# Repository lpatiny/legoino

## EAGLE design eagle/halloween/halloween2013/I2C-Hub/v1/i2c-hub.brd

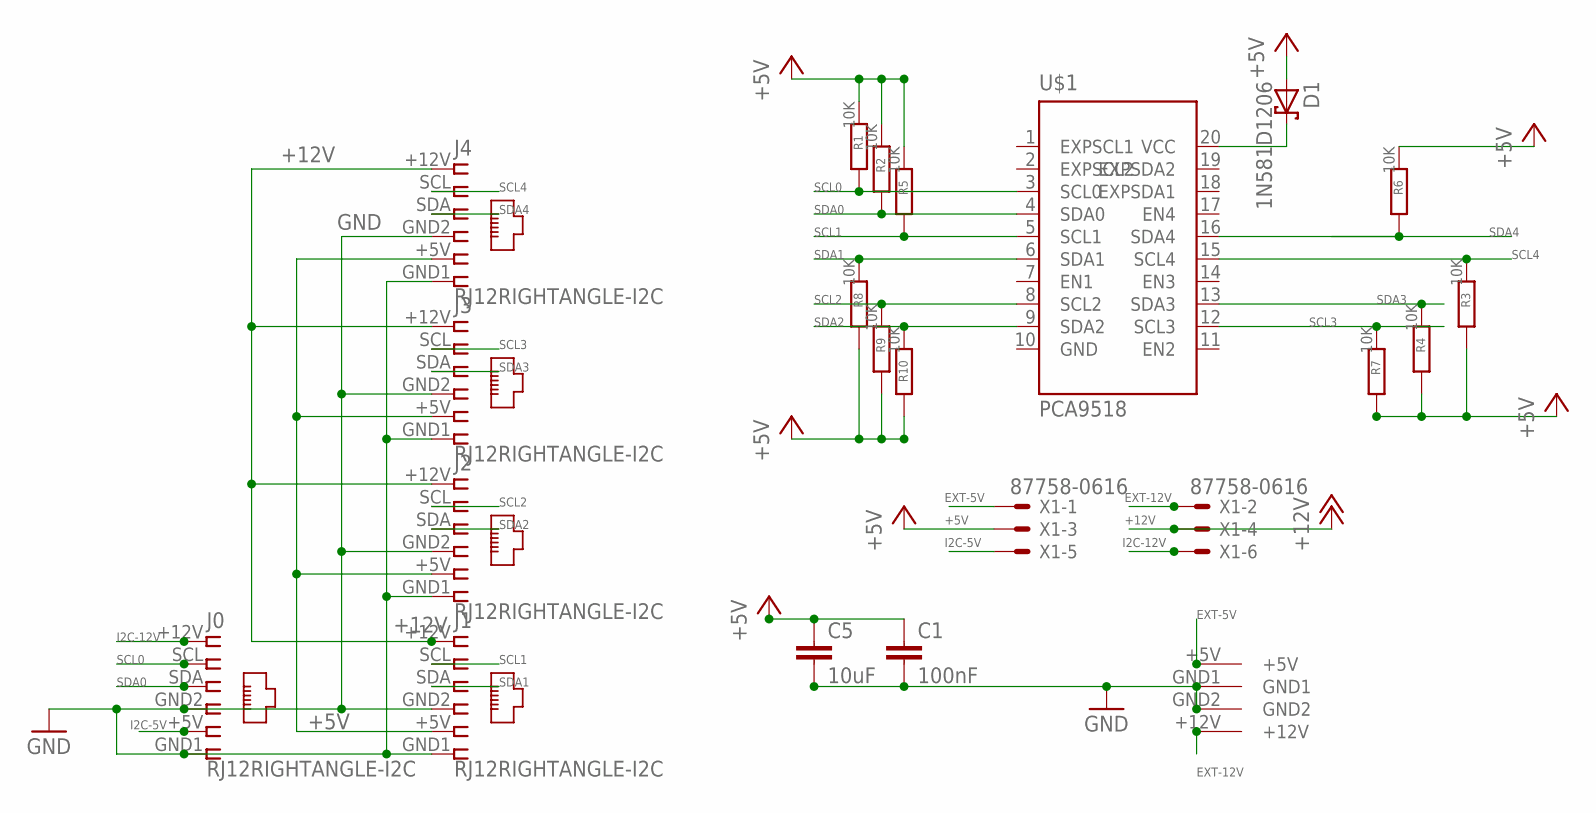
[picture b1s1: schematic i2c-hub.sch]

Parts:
C1: 100nF; C1206
C5: 10uF; C1206
D1: 1N581D1206; LED-1206
J0, J1, J2, J3, J4: RJ12RIGHTANGLE-I2C; RJ12-RIGHTANGLE-I2C
R1, R2, R3, R4, R5, R6, R7, R8, R9, R10: 10K; M1206
U$1: PCA9518; SO20W
U$2: KPJX-4S-S
X1: 87758-0616

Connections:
+5V: C1.1, C5.1, D1.A, J1.+5V (5), J2.+5V (5), J3.+5V (5), J4.+5V (5), R1.1, R2.1, R3.2, R4.2, R5.1, R6.1, R7.2, R8.2, R9.2, R10.2, X1.3
+5V1: D1.C, U$1.20 (VCC)
+12V: J1.+12V (1), J2.+12V (1), J3.+12V (1), J4.+12V (1), X1.4
EXT-5V: U$2.+5V, X1.1
EXT-12V: U$2.+12V, X1.2
GND: C1.2, C5.2, J0.GND1 (6), J0.GND2 (4), J1.GND1 (6), J1.GND2 (4), J2.GND1 (6), J2.GND2 (4), J3.GND1 (6), J3.GND2 (4), J4.GND1 (6), J4.GND2 (4), U$1.10 (GND), U$2.GND1, U$2.GND2
I2C-5V: J0.+5V (5), X1.5
I2C-12V: J0.+12V (1), X1.6
SCL0: J0.SCL (2), R1.2, U$1.3 (SCL0)
SCL1: J1.SCL (2), R5.2, U$1.5 (SCL1)
SCL2: J2.SCL (2), R9.1, U$1.8 (SCL2)
SCL3: J3.SCL (2), R7.1, U$1.12 (SCL3)
SCL4: J4.SCL (2), R3.1, U$1.15 (SCL4)
SDA0: J0.SDA (3), R2.2, U$1.4 (SDA0)
SDA1: J1.SDA (3), R8.1, U$1.6 (SDA1)
SDA2: J2.SDA (3), R10.1, U$1.9 (SDA2)
SDA3: J3.SDA (3), R4.1, U$1.13 (SDA3)
SDA4: J4.SDA (3), R6.2, U$1.16 (SDA4)

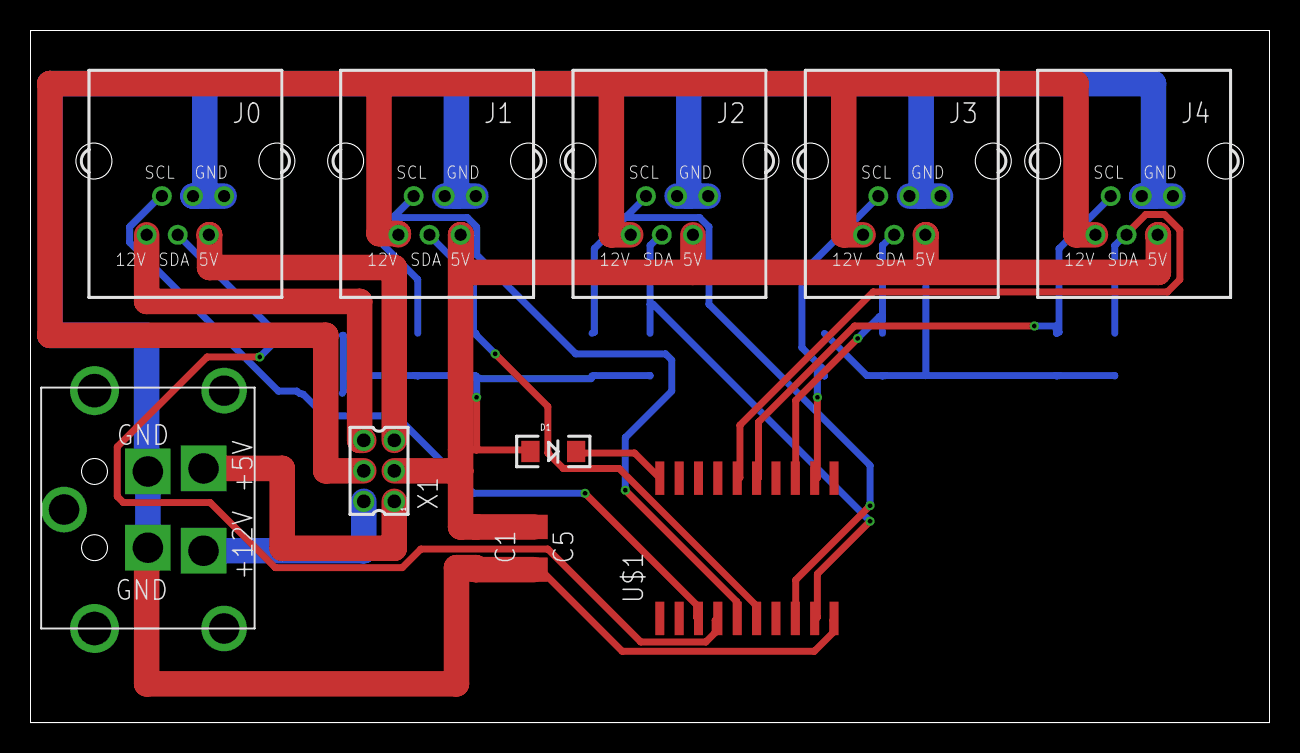
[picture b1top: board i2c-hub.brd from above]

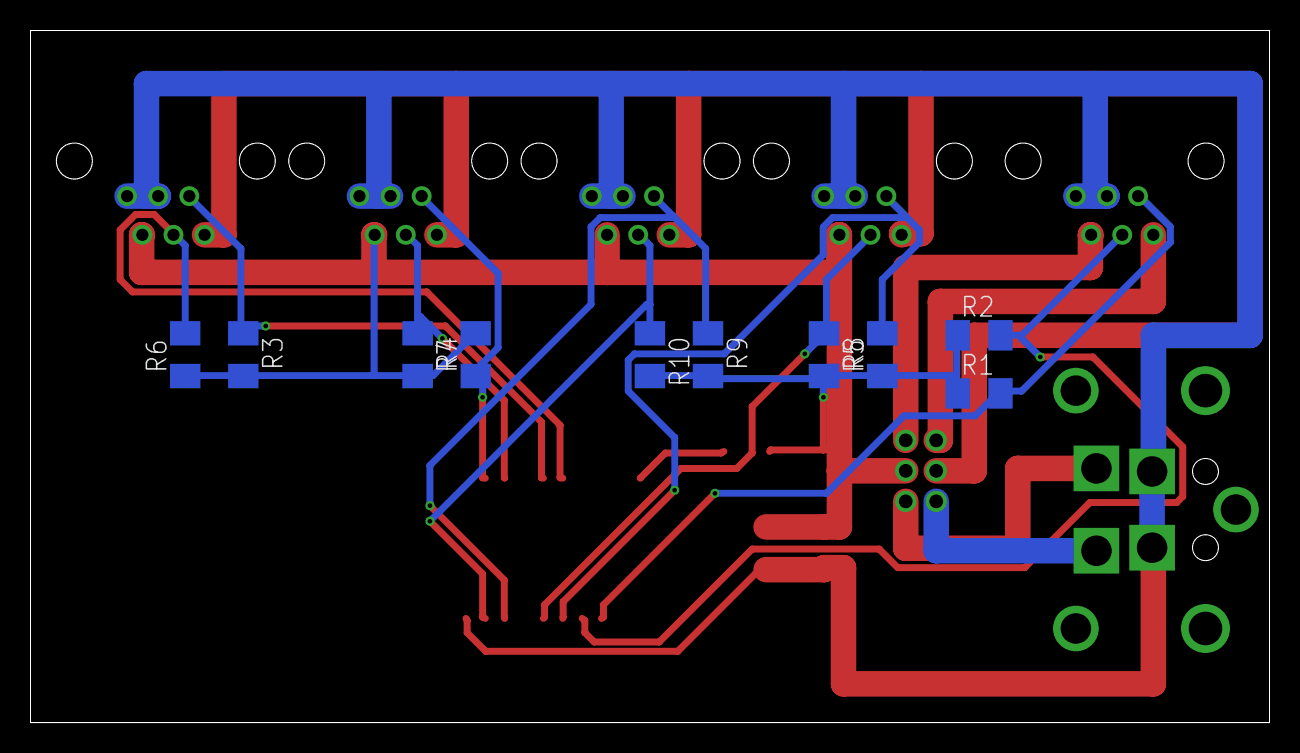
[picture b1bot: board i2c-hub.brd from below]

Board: 2 copper layers, 81.3 x 45.4 mm, 21 parts (10 on the bottom side), 18 nets.

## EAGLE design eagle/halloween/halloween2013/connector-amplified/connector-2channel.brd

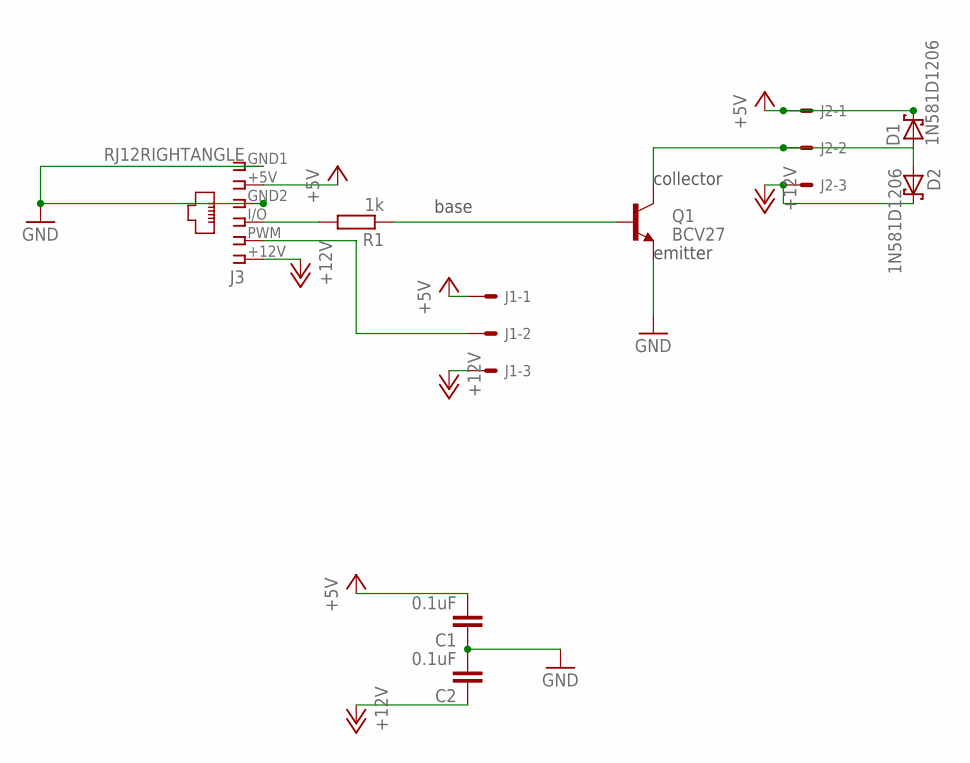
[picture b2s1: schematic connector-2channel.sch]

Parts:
C1, C2: 0.1uF; C1206
D1, D2: 1N581D1206; LED-1206
J1, J2: 22-27-2031-03; 6410-03
J3: RJ12RIGHTANGLE; RJ12-RIGHTANGLE
Q1: BCV27; SOT23
R1: 1k; M1206

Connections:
+5V: C1.2, D1.C, J1.1, J2.1, J3.+5V (5)
+12V: C2.1, D2.C, J1.3, J2.3, J3.+12V (1)
GND: C1.1, C2.2, J3.GND1 (6), J3.GND2 (4), Q1.2 (E)
unnamed: Q1.1 (B), R1.1
unnamed: J3.I/O (3), R1.2
unnamed: J1.2, J3.PWM (2)
unnamed: D1.A, D2.A, J2.2, Q1.3 (C)

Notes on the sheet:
base
collector
emitter

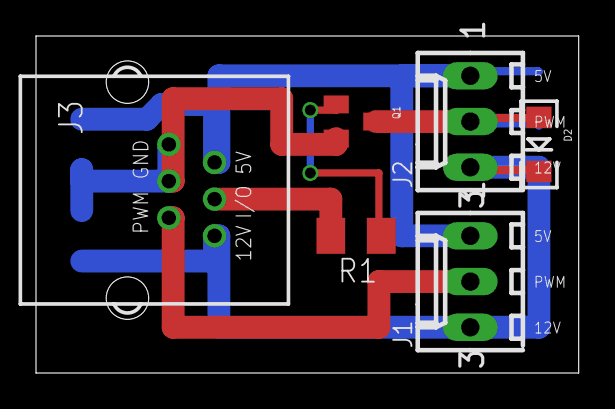
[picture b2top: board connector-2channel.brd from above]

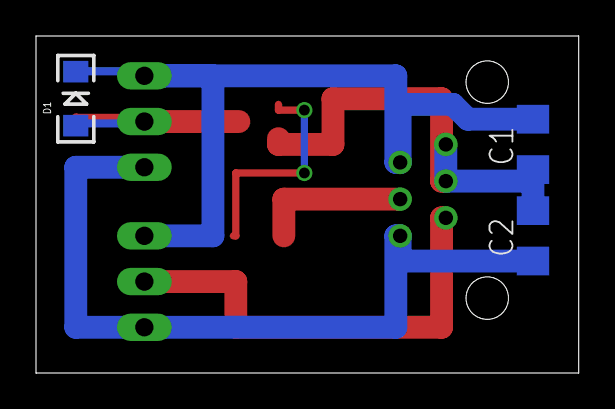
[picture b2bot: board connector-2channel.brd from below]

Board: 2 copper layers, 30.1 x 18.7 mm, 9 parts (3 on the bottom side), 7 nets.

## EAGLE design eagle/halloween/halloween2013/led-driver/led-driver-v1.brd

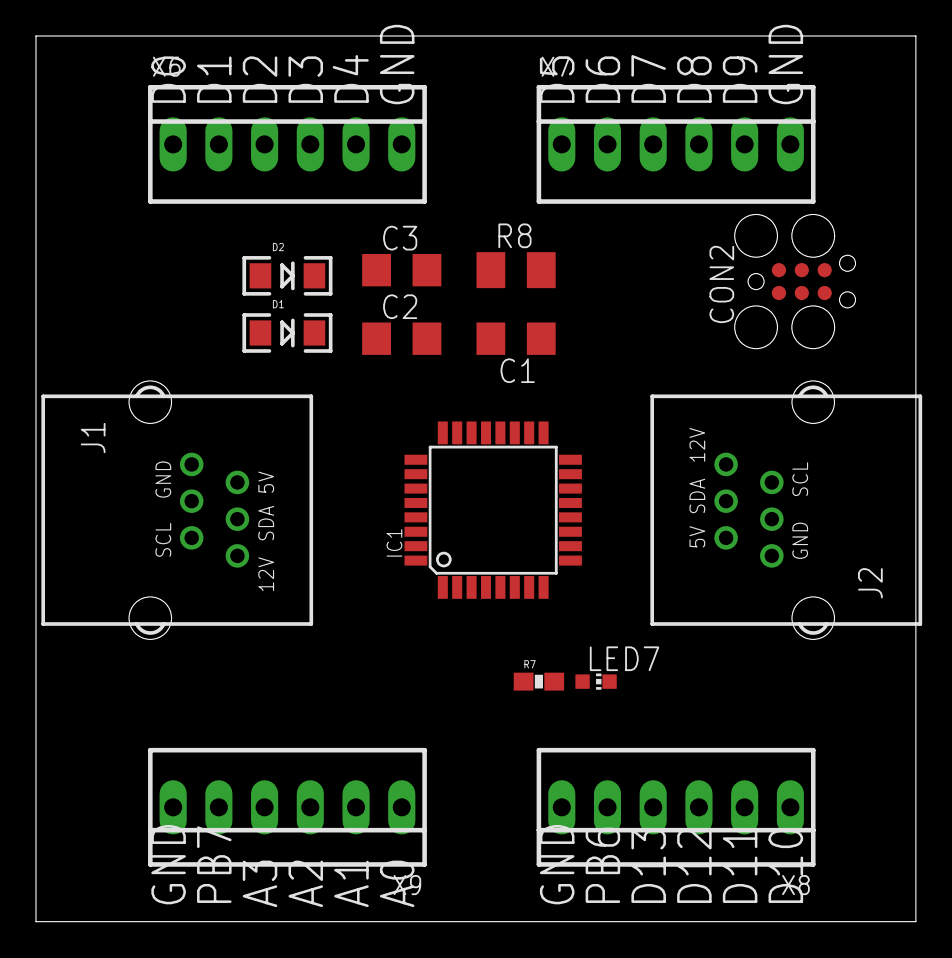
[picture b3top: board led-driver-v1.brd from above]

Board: 2 copper layers, 48.9 x 49.2 mm, 16 parts (0 on the bottom side), 30 nets, no tracks yet.

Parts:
C1, C2: 0.1uF; C1206
C3: 10uF; C1206
CON2: TC2030-MCP
D1, D2: 1N581D1206; LED-1206
IC1: MEGA8-AI; TQFP32-08
J1, J2: RJ12RIGHTANGLE-I2C; RJ12-RIGHTANGLE-I2C
LED7: CHIP-LED0603
R7: 10k; 0603-RES
R8: 10k; M1206
X6, X7, X8, X9: 22-23-2061

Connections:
5V_A: CON2.5V, D1.A
5V_B: D2.A, J1.+5V, J2.+5V
+5V: C1.1, C2.1, C3.1, D1.C, D2.C, IC1.4, IC1.6, IC1.18, R7.1, R8.2
A0: IC1.23, X9.1
A1: IC1.24, X9.2
A2: IC1.25, X9.3
A3: IC1.26, X9.4
D0: IC1.30, X6.1
D1: IC1.31, X6.2
D2: IC1.32, X6.3
D3: IC1.1, X6.4
D4: IC1.2, X6.5
D5: IC1.9, X7.1
D6: IC1.10, X7.2
D7: IC1.11, X7.3
D8: IC1.12, X7.4
D9: IC1.13, X7.5
D10: IC1.14, X8.1
GND: C2.2, C3.2, CON2.GND, IC1.3, IC1.5, IC1.21, J1.GND1, J1.GND2, J2.GND1, J2.GND2, LED7.C, X6.6, X7.6, X8.6, X9.6
MISO: CON2.MISO, IC1.16, X8.3
MOSI: CON2.MOSI, IC1.15, X8.2
unnamed: C1.2, IC1.20
unnamed: J1.+12V, J2.+12V
unnamed: LED7.A, R7.2
PB6: IC1.7, X8.5
PB7: IC1.8, X9.5
RESET: CON2.RESET, IC1.29, R8.1
SCK: CON2.SCK, IC1.17, X8.4
SCL: IC1.28, J1.SCL, J2.SCL
SDA: IC1.27, J1.SDA, J2.SDA

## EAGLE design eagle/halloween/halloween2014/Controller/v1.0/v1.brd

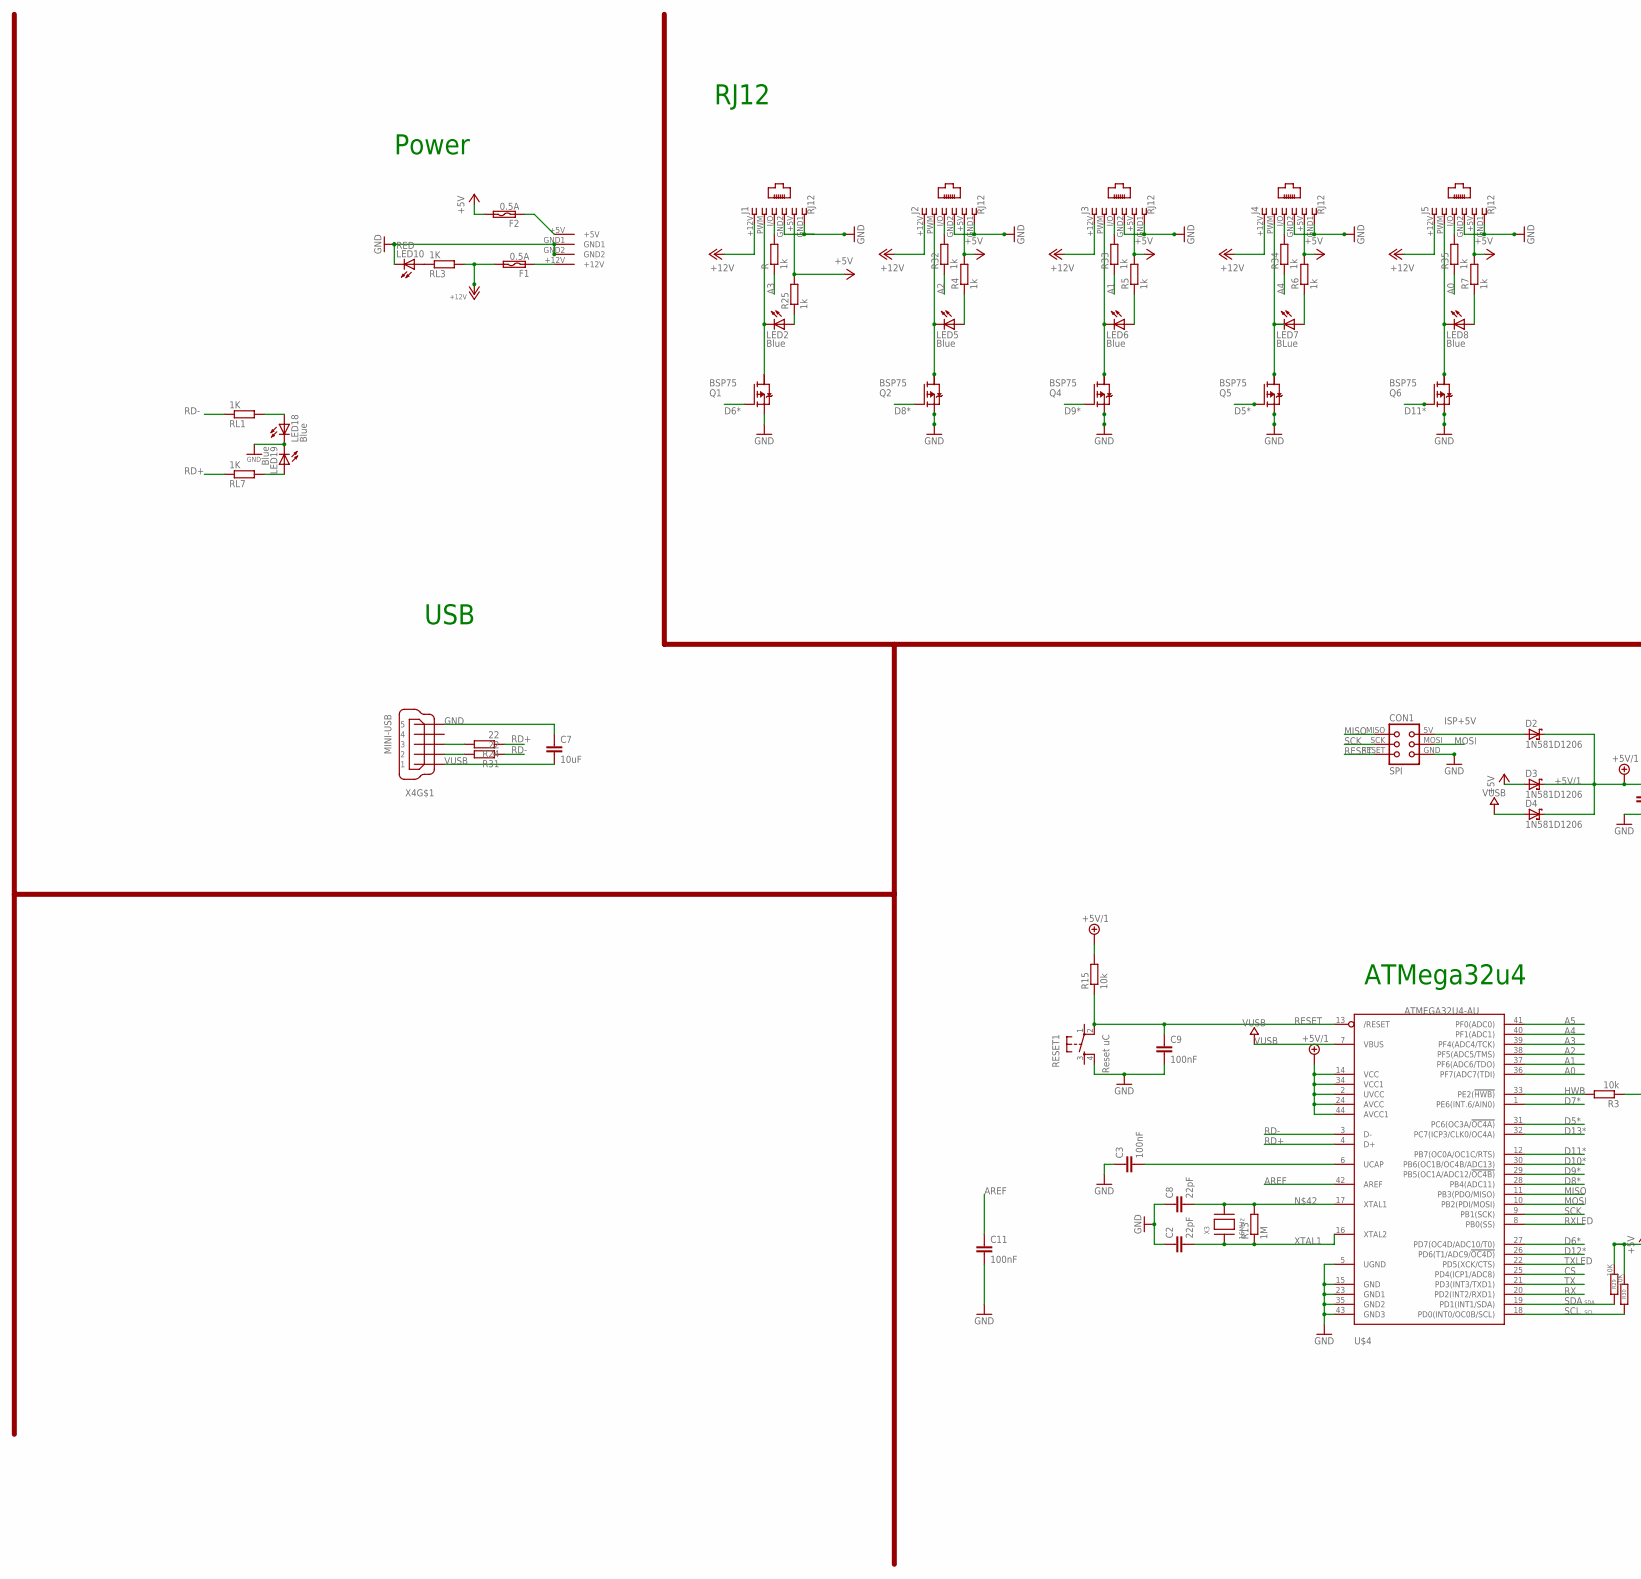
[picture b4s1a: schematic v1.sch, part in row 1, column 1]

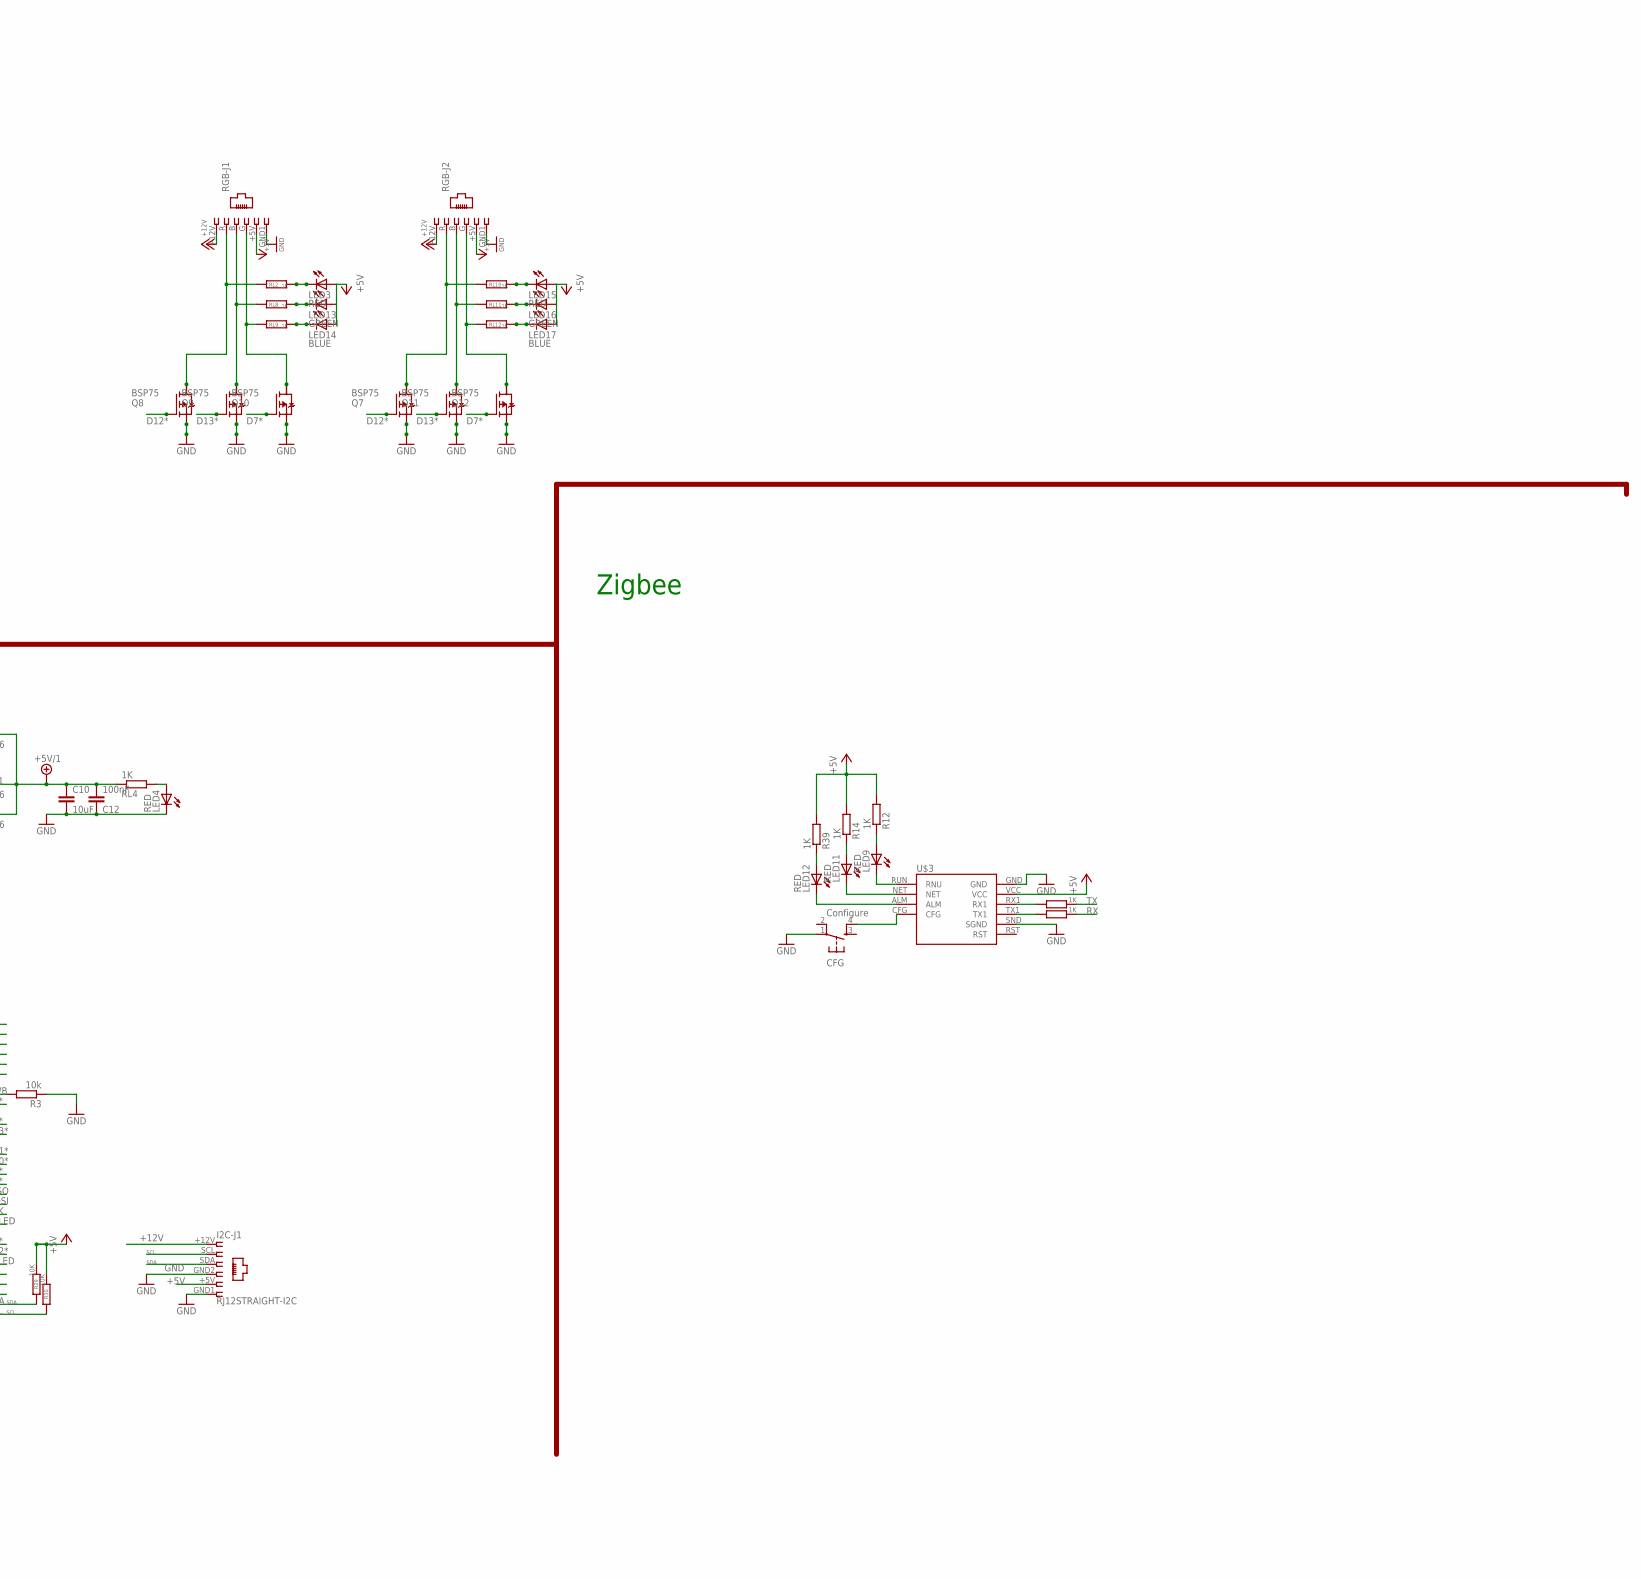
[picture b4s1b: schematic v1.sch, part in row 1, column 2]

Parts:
C2, C8: 22pF; C1206
C3, C9, C11, C12: 100nF; C1206
C7, C10: 10uF; C1206
CFG: Configure; TACTILE_SWITCH_SMD
CON1: SPI; TC2030-MCP-NL
D2, D3, D4: 1N581D1206; LED-1206
F1, F2: 0.5A; C1812
I2C-J1: RJ12STRAIGHT-I2C; RJ12-STRAIGHT-I2C
J1, J2, J3, J4, J5: RJ12; RJ12-STRAIGHT
LED2, LED5, LED6, LED8, LED18, LED19: Blue; CHIPLED_1206
LED3, LED4, LED10, LED15: RED; CHIPLED_1206
LED7: BLue; CHIPLED_1206
LED9, LED11, LED12: RED; CHIP-LED0805
LED13, LED16: GREEN; CHIPLED_1206
LED14, LED17: BLUE; CHIPLED_1206
Q1, Q2, Q4, Q5, Q6, Q7, Q8, Q9, Q10, Q11, Q12: BSP75; PG-SOT-223
R, R4, R5, R6, R7, R25, R32, R33, R34, R35: 1k; R0805
R3, R15: 10k; M0805
R8, R11, R12, R14, R39: 1K; R0805
R13: 1M; R1206
R24, R31: 22; M1206
R29, R30: 10K; M0805
RESET1: Reset uC; TACTILE_SWITCH_SMD
RGB-J1, RGB-J2: RJ12; RJ12-STRAIGHT-RGB
RL1, RL3, RL4, RL7: 1K; R0805
RL2, RL8, RL9, RL10, RL11, RL12: 1K; M0805
U$3: SZ05-ZIGBEESMD; SZ05-ZIGBEE3
U$4: ATMEGA32U4-AU; TQFP44
U$6: KPJX-4S-S
X3: 16MHz; NX6035
X4: MINI-USB; 32005-201

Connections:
+5V: D3.A, F2.2, I2C-J1.+5V (5), J1.+5V (5), J2.+5V (5), J3.+5V (5), J4.+5V (5), J5.+5V (5), LED3.A, LED13.A, LED14.A, LED15.A, LED16.A, LED17.A, R4.2, R5.2, R6.2, R7.2, R12.2, R14.2, R25.2, R29.1, R30.1, R39.2, RGB-J1.+5V (5), RGB-J2.+5V (5), U$3.VCC
+5V/1: C10.1, C12.2, D2.C, D3.C, D4.C, R15.2, RL4.1, U$4.2 (UVCC), U$4.14 (VCC), U$4.24 (AVCC), U$4.34 (VCC1), U$4.44 (AVCC1)
+12V: F1.2, I2C-J1.+12V (1), J1.+12V (1), J2.+12V (1), J3.+12V (1), J4.+12V (1), J5.+12V (1), RGB-J1.+12V (1), RGB-J2.+12V (1), RL3.2
A0: R35.1, U$4.36 (PF7(ADC7(TDI))
A1: R33.1, U$4.37 (PF6(ADC6/TDO))
A2: R32.1, U$4.38 (PF5(ADC5/TMS))
A3: R.1, U$4.39 (PF4(ADC4/TCK))
A4: R34.1, U$4.40 (PF1(ADC1))
A5: U$4.41 (PF0(ADC0))
AREF: C11.1, U$4.42 (AREF)
CS: U$4.25 (PD4(ICP1/ADC8))
D5*: Q5.1 (G), U$4.31 (PC6(OC3A/!OC4A))
D6*: Q1.1 (G), U$4.27 (PD7(OC4D/ADC10/T0))
D7*: Q10.1 (G), Q12.1 (G), U$4.1 (PE6(INT.6/AIN0))
D8*: Q2.1 (G), U$4.28 (PB4(ADC11))
D9*: Q4.1 (G), U$4.29 (PB5(OC1A/ADC12/!OC4B))
D10*: U$4.30 (PB6(OC1B/OC4B/ADC13))
D11*: Q6.1 (G), U$4.12 (PB7(OC0A/OC1C/RTS))
D12*: Q7.1 (G), Q8.1 (G), U$4.26 (PD6(T1/ADC9/!OC4D))
D13*: Q9.1 (G), Q11.1 (G), U$4.32 (PC7(ICP3/CLK0/OC4A))
D+USB: R24.2, X4.3
D-USB: R31.2, X4.2
GND: C2.1, C3.1, C7.1, C8.1, C9.2, C10.2, C11.2, C12.1, CFG.1, CON1.GND, I2C-J1.GND1 (6), I2C-J1.GND2 (4), J1.GND1 (6), J1.GND2 (4), J2.GND1 (6), J2.GND2 (4), J3.GND1 (6), J3.GND2 (4), J4.GND1 (6), J4.GND2 (4), J5.GND1 (6), J5.GND2 (4), LED4.C, LED10.C, LED18.C, LED19.C, Q1.3 (S), Q2.3 (S), Q4.3 (S), Q5.3 (S), Q6.3 (S), Q7.3 (S), Q8.3 (S), Q9.3 (S), Q10.3 (S), Q11.3 (S), Q12.3 (S), R3.1, RESET1.4, RGB-J1.GND1 (6), RGB-J2.GND1 (6), U$3.GND, U$3.SND (SGND), U$4.5 (UGND), U$4.15 (GND), U$4.23 (GND1), U$4.35 (GND2), U$4.43 (GND3), U$6.GND1, U$6.GND2, X4.5
GND1: LED9.C, U$3.RUN (RNU)
GND2: LED11.C, U$3.NET
GND3: LED12.C, U$3.ALM
HWB: R3.2, U$4.33 (PE2(!HWB))
ISP+5V: CON1.5V (VCC), D2.A
MISO: CON1.MISO, U$4.11 (PB3(PDO/MISO))
MOSI: CON1.MOSI, U$4.10 (PB2(PDI/MOSI))
unnamed: J3.PWM (2), LED6.C, Q4.2 (D)
unnamed: J2.I/O (3), R32.2
unnamed: LED5.A, R4.1
unnamed: J4.PWM (2), LED7.C, Q5.2 (D)
unnamed: Q10.2 (D), RGB-J1.G (4), RL9.1
unnamed: J3.I/O (3), R33.2
unnamed: LED18.A, RL1.2
unnamed: Q11.2 (D), RGB-J2.B (3), RL11.1
unnamed: R11.2, U$3.RX1
unnamed: LED4.A, RL4.2
unnamed: LED19.A, RL7.2
unnamed: C3.2, U$4.6 (UCAP)
unnamed: LED2.A, R25.1
unnamed: J1.I/O (3), R.2
unnamed: J5.PWM (2), LED8.C, Q6.2 (D)
unnamed: Q7.2 (D), RGB-J2.R (2), RL10.1
unnamed: LED6.A, R5.1
unnamed: Q12.2 (D), RGB-J2.G (4), RL12.1
unnamed: R8.2, U$3.TX1
unnamed: LED9.A, R12.1
unnamed: LED11.A, R14.1
unnamed: LED12.A, R39.1
unnamed: J2.PWM (2), LED5.C, Q2.2 (D)
unnamed: J4.I/O (3), R34.2
unnamed: LED7.A, R6.1
unnamed: LED15.C, RL10.2
unnamed: J5.I/O (3), R35.2
unnamed: LED8.A, R7.1
unnamed: J1.PWM (2), LED2.C, Q1.2 (D)
unnamed: CFG.4, U$3.CFG
unnamed: LED3.C, RL2.2
unnamed: LED13.C, RL8.2
unnamed: F2.1, U$6.+5V
unnamed: F1.1, U$6.+12V
unnamed: LED14.C, RL9.2
unnamed: LED16.C, RL11.2
unnamed: C8.2, R13.2, U$4.17 (XTAL1), X3.P$2
unnamed: LED17.C, RL12.2
unnamed: Q9.2 (D), RGB-J1.B (3), RL8.1
unnamed: Q8.2 (D), RGB-J1.R (2), RL2.1
unnamed: LED10.A, RL3.1
RD+: R24.1, RL7.1, U$4.4 (D+)
RD-: R31.1, RL1.1, U$4.3 (D-)
RESET: C9.1, CON1.RESET, R15.1, RESET1.2, U$4.13 (/RESET)
RX: R8.1, U$4.20 (PD2(INT2/RXD1))
RXLED: U$4.8 (PB0(SS))
SCK: CON1.SCK, U$4.9 (PB1(SCK))
SCL: I2C-J1.SCL (2), R30.2, U$4.18 (PD0(INT0/OC0B/SCL))
SDA: I2C-J1.SDA (3), R29.2, U$4.19 (PD1(INT1/SDA))
TX: R11.1, U$4.21 (PD3(INT3/TXD1))
TXLED: U$4.22 (PD5(XCK/CTS))
VUSB: C7.2, D4.A, U$4.7 (VBUS), X4.1
XTAL1: C2.2, R13.1, U$4.16 (XTAL2), X3.P$1

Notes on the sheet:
RJ12
ATMega32u4
USB
Power
Zigbee

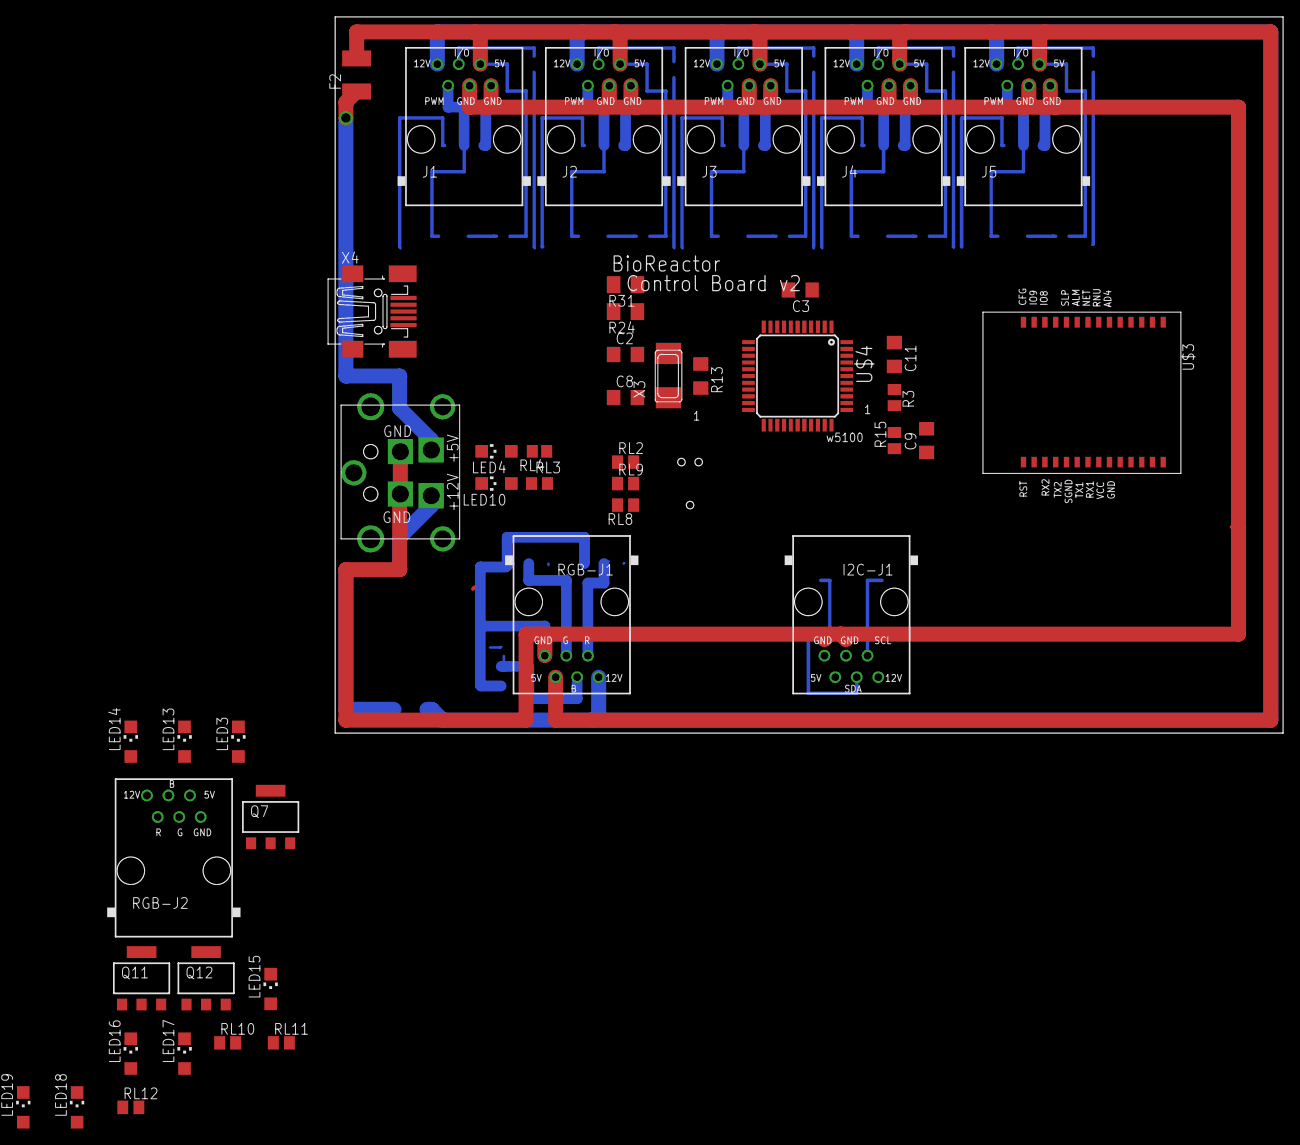
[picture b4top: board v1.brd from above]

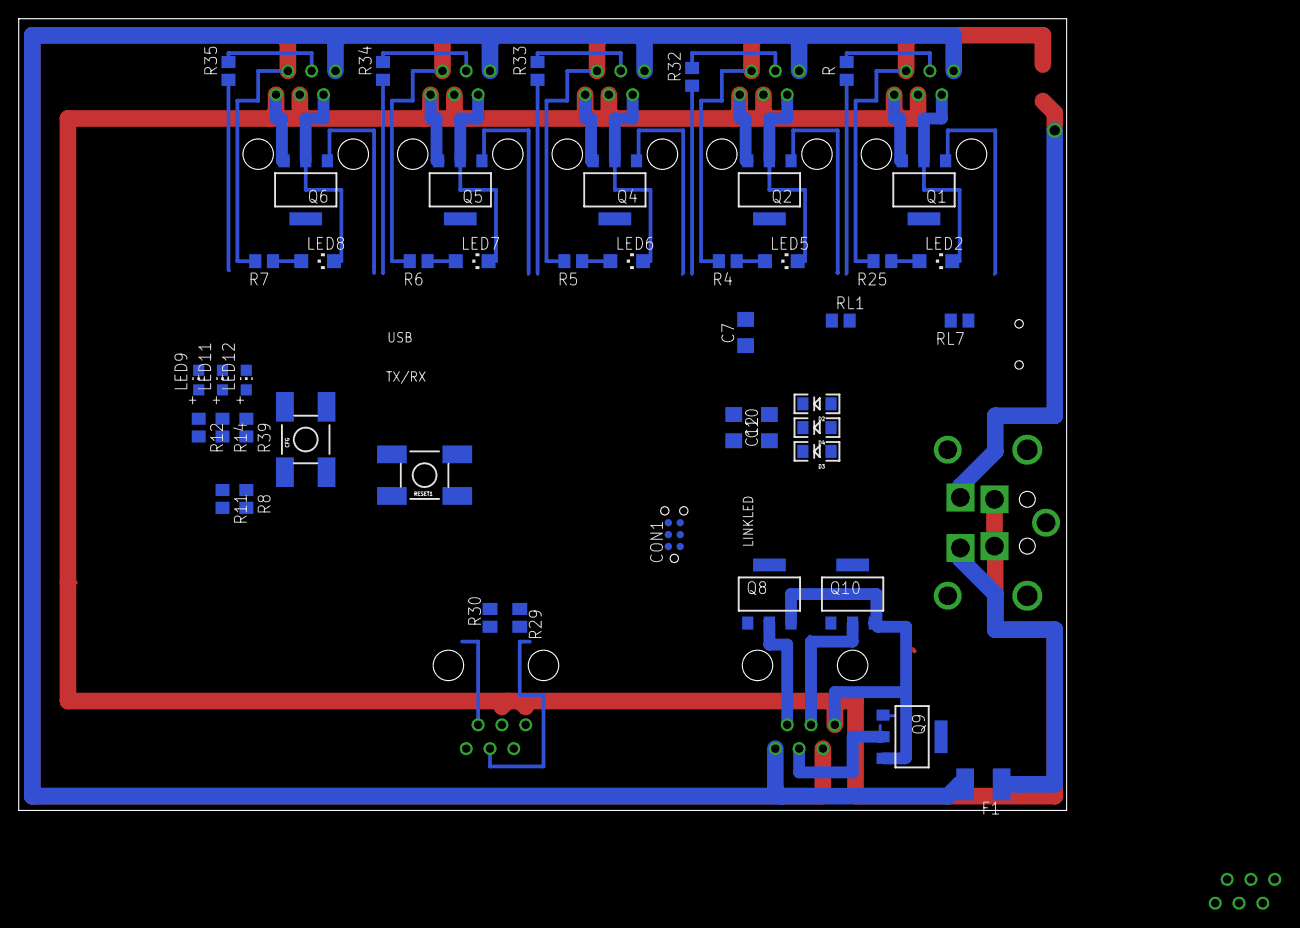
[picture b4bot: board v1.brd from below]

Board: 2 copper layers, 111.9 x 84.6 mm, 90 parts (45 on the bottom side), 78 nets.

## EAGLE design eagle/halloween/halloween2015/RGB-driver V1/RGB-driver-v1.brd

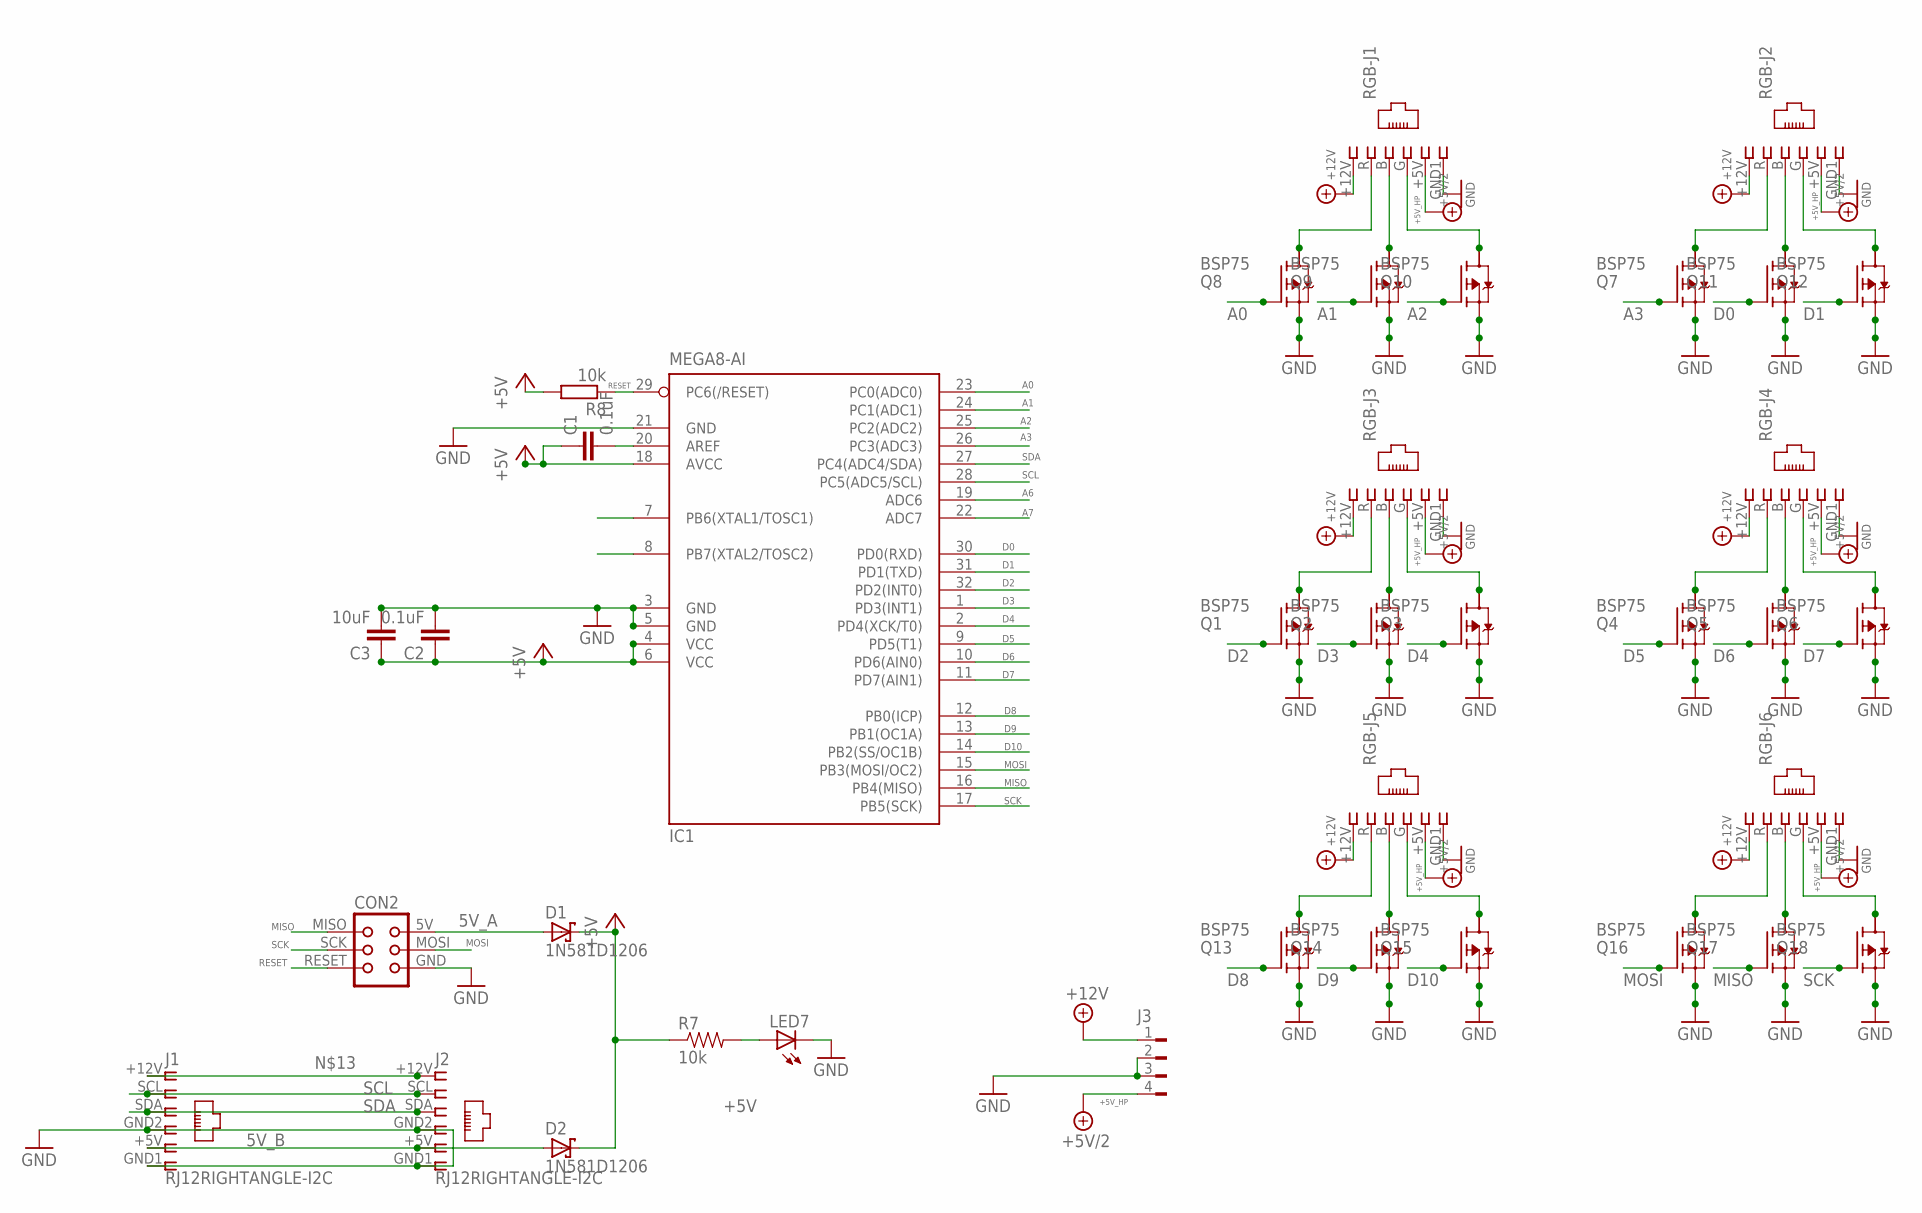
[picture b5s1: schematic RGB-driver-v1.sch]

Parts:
C1, C2: 0.1uF; C1206
C3: 10uF; C1206
CON2: TINYISPTAG; TC2030-MCP
D1, D2: 1N581D1206; LED-1206
IC1: MEGA8-AI; TQFP32-08
J1, J2: RJ12RIGHTANGLE-I2C; RJ12-RIGHTANGLE-I2C
J3: FLOP-4W827001; 827001
LED7: LEDCHIP-LED0603; CHIP-LED0603
Q1, Q2, Q3, Q4, Q5, Q6, Q7, Q8, Q9, Q10, Q11, Q12, Q13, Q14, Q15, Q16, Q17, Q18: BSP75; PG-SOT-223
R7: 10k; 0603-RES
R8: 10k; M1206
RGB-J1, RGB-J2, RGB-J3, RGB-J4, RGB-J5, RGB-J6: RJ12; RJ12-STRAIGHT-RGB

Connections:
5V_A: CON2.5V (VCC), D1.A
5V_B: D2.A, J1.+5V (5), J2.+5V (5)
+5V: C1.1, C2.1, C3.1, D1.C, D2.C, IC1.4 (VCC), IC1.6 (VCC), IC1.18 (AVCC), R7.1, R8.2
+5V_HP: J3.4, RGB-J1.+5V (5), RGB-J2.+5V (5), RGB-J3.+5V (5), RGB-J4.+5V (5), RGB-J5.+5V (5), RGB-J6.+5V (5)
+12V_HP: J3.1, RGB-J1.+12V (1), RGB-J2.+12V (1), RGB-J3.+12V (1), RGB-J4.+12V (1), RGB-J5.+12V (1), RGB-J6.+12V (1)
A0: IC1.23 (PC0(ADC0)), Q8.1 (G)
A1: IC1.24 (PC1(ADC1)), Q9.1 (G)
A2: IC1.25 (PC2(ADC2)), Q10.1 (G)
A3: IC1.26 (PC3(ADC3)), Q7.1 (G)
A6: IC1.19 (ADC6)
A7: IC1.22 (ADC7)
D0: IC1.30 (PD0(RXD)), Q11.1 (G)
D1: IC1.31 (PD1(TXD)), Q12.1 (G)
D2: IC1.32 (PD2(INT0)), Q1.1 (G)
D3: IC1.1 (PD3(INT1)), Q2.1 (G)
D4: IC1.2 (PD4(XCK/T0)), Q3.1 (G)
D5: IC1.9 (PD5(T1)), Q4.1 (G)
D6: IC1.10 (PD6(AIN0)), Q5.1 (G)
D7: IC1.11 (PD7(AIN1)), Q6.1 (G)
D8: IC1.12 (PB0(ICP)), Q13.1 (G)
D9: IC1.13 (PB1(OC1A)), Q14.1 (G)
D10: IC1.14 (PB2(SS/OC1B)), Q15.1 (G)
GND: C2.2, C3.2, CON2.GND, IC1.3 (GND), IC1.5 (GND), IC1.21 (GND), J1.GND1 (6), J1.GND2 (4), J2.GND1 (6), J2.GND2 (4), J3.2, J3.3, LED7.C, Q1.3 (S), Q2.3 (S), Q3.3 (S), Q4.3 (S), Q5.3 (S), Q6.3 (S), Q7.3 (S), Q8.3 (S), Q9.3 (S), Q10.3 (S), Q11.3 (S), Q12.3 (S), Q13.3 (S), Q14.3 (S), Q15.3 (S), Q16.3 (S), Q17.3 (S), Q18.3 (S), RGB-J1.GND1 (6), RGB-J2.GND1 (6), RGB-J3.GND1 (6), RGB-J4.GND1 (6), RGB-J5.GND1 (6), RGB-J6.GND1 (6)
MISO: CON2.MISO, IC1.16 (PB4(MISO)), Q17.1 (G)
MOSI: CON2.MOSI, IC1.15 (PB3(MOSI/OC2)), Q16.1 (G)
unnamed: Q2.2 (D), RGB-J3.B (3)
unnamed: Q1.2 (D), RGB-J3.R (2)
unnamed: Q3.2 (D), RGB-J3.G (4)
unnamed: C1.2, IC1.20 (AREF)
unnamed: Q5.2 (D), RGB-J4.B (3)
unnamed: Q10.2 (D), RGB-J1.G (4)
unnamed: Q4.2 (D), RGB-J4.R (2)
unnamed: Q6.2 (D), RGB-J4.G (4)
unnamed: Q14.2 (D), RGB-J5.B (3)
unnamed: Q11.2 (D), RGB-J2.B (3)
unnamed: Q13.2 (D), RGB-J5.R (2)
unnamed: Q15.2 (D), RGB-J5.G (4)
unnamed: J1.+12V (1), J2.+12V (1)
unnamed: Q17.2 (D), RGB-J6.B (3)
unnamed: LED7.A, R7.2
unnamed: Q16.2 (D), RGB-J6.R (2)
unnamed: Q18.2 (D), RGB-J6.G (4)
unnamed: Q7.2 (D), RGB-J2.R (2)
unnamed: Q12.2 (D), RGB-J2.G (4)
unnamed: Q9.2 (D), RGB-J1.B (3)
unnamed: Q8.2 (D), RGB-J1.R (2)
PB6: IC1.7 (PB6(XTAL1/TOSC1))
PB7: IC1.8 (PB7(XTAL2/TOSC2))
RESET: CON2.RESET, IC1.29 (PC6(/RESET)), R8.1
SCK: CON2.SCK, IC1.17 (PB5(SCK)), Q18.1 (G)
SCL: IC1.28 (PC5(ADC5/SCL)), J1.SCL (2), J2.SCL (2)
SDA: IC1.27 (PC4(ADC4/SDA)), J1.SDA (3), J2.SDA (3)

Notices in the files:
parts and their libraries:
SparkFun: Licensing: CC v3.0 Share-Alike You are welcome to use this library for commercial purposes.
lpatiny: ©2009 ROFA.cz - modified and updated by Robert Darlington ‹rdarlington@gmail.com›
lpatiny: Â©2009 ROFA.cz - modified and updated by Robert Darlington ‹rdarlington@gmail.com›
